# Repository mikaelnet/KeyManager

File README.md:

# KeyManager
Key/password manager on a USB stick

Based on V-USB (https://www.obdev.at/products/vusb/) and DIY USB password generator (http://codeandlife.com/2012/03/03/diy-usb-password-generator/)

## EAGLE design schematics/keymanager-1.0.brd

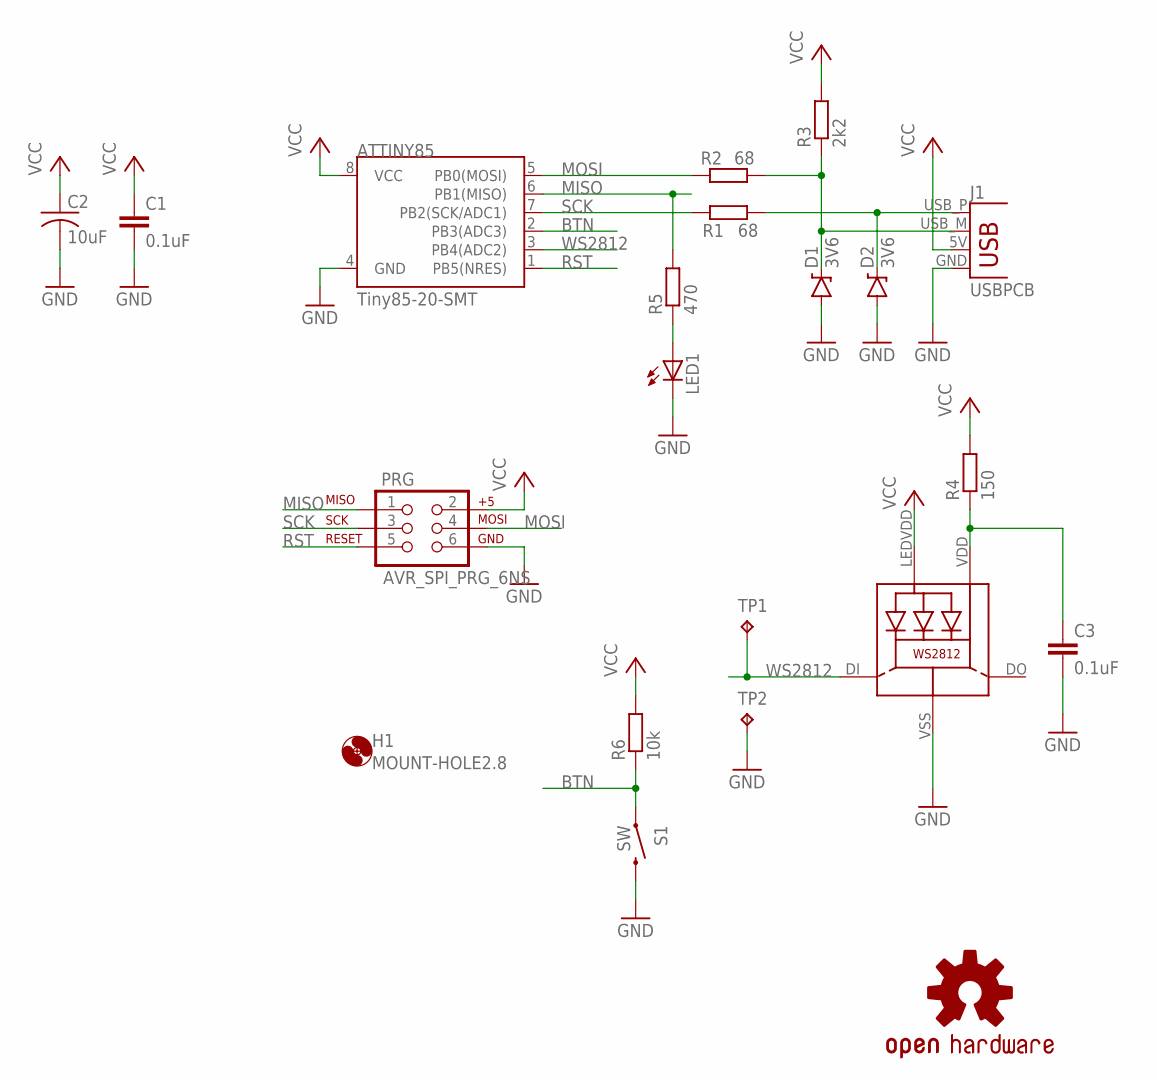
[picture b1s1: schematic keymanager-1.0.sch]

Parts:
ATTINY85: Tiny85-20-SMT; SO08-EIAJ
C1, C3: 0.1uF; C1206
C2: 10uF; C1206
D1, D2: 3V6; SOD-323
H1: MOUNT-HOLE2.8; 2,8
J1: USBPCB; USB-A-PCB
LED1: LEDSMT1206; 1206
LOGO1: OSHW-LOGOS; OSHW-LOGO-S
PRG: AVR_SPI_PRG_6NS; 2X3-NS
R1, R2: 68; R1206
R3: 2k2; R1206
R4: 150; R1206
R5: 470; R1206
R6: 10k; R1206
S1: SW; TACTILE-SWITCH-SMD
TP1, TP2: TPB1,27; B1,27
WS2812: WS2812

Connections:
BTN: ATTINY85.2 (PB3(ADC3)), R6.1, S1.1
D+: D2.C, J1.USB_P (D+), R1.2
D-: D1.C, J1.USB_M (D-), R2.2, R3.1
GND: ATTINY85.4 (GND), C1.2, C2.2, C3.2, D1.A, D2.A, J1.GND, LED1.C, PRG.6, S1.3 (2), TP2.TP, WS2812.VSS (GND)
MISO: ATTINY85.6 (PB1(MISO)), PRG.1, R5.2
MOSI: ATTINY85.5 (PB0(MOSI)), PRG.4, R2.1
unnamed: C3.1, R4.1, WS2812.VDD
unnamed: LED1.A, R5.1
RST: ATTINY85.1 (PB5(NRES)), PRG.5
SCK: ATTINY85.7 (PB2(SCK/ADC1)), PRG.3, R1.1
VCC: ATTINY85.8 (VCC), C1.1, C2.1, J1.5V (VBUS), PRG.2, R3.2, R4.2, R6.2, WS2812.LEDVDD
WS2812: ATTINY85.3 (PB4(ADC2)), TP1.TP, WS2812.DI

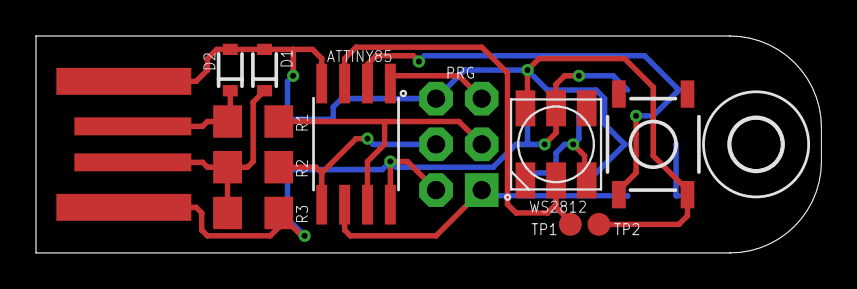
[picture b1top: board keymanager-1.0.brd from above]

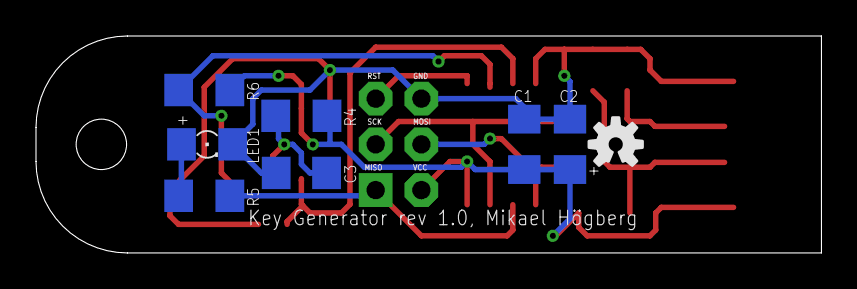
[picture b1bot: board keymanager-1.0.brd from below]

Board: 2 copper layers, 43.6 x 12.1 mm, 21 parts (8 on the bottom side), 12 nets.

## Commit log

2016-08-18 stub commit
2016-08-19 Added solution file
2016-08-19 Added 16.5MHz support
2016-08-19 Added ws2812 code
2016-08-19 Added toggle logic
2016-08-19 Changed to Studio 6.1 and added password stub code
2016-08-20 Updated event code
2016-08-21 Password generation, faster printout
2016-08-23 Added process files

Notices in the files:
parts and their libraries:
SparkFun-DigitalIC: Licensing: Creative Commons ShareAlike 4.0 International - https://creativecommons.org/licenses/by-sa/4.0
